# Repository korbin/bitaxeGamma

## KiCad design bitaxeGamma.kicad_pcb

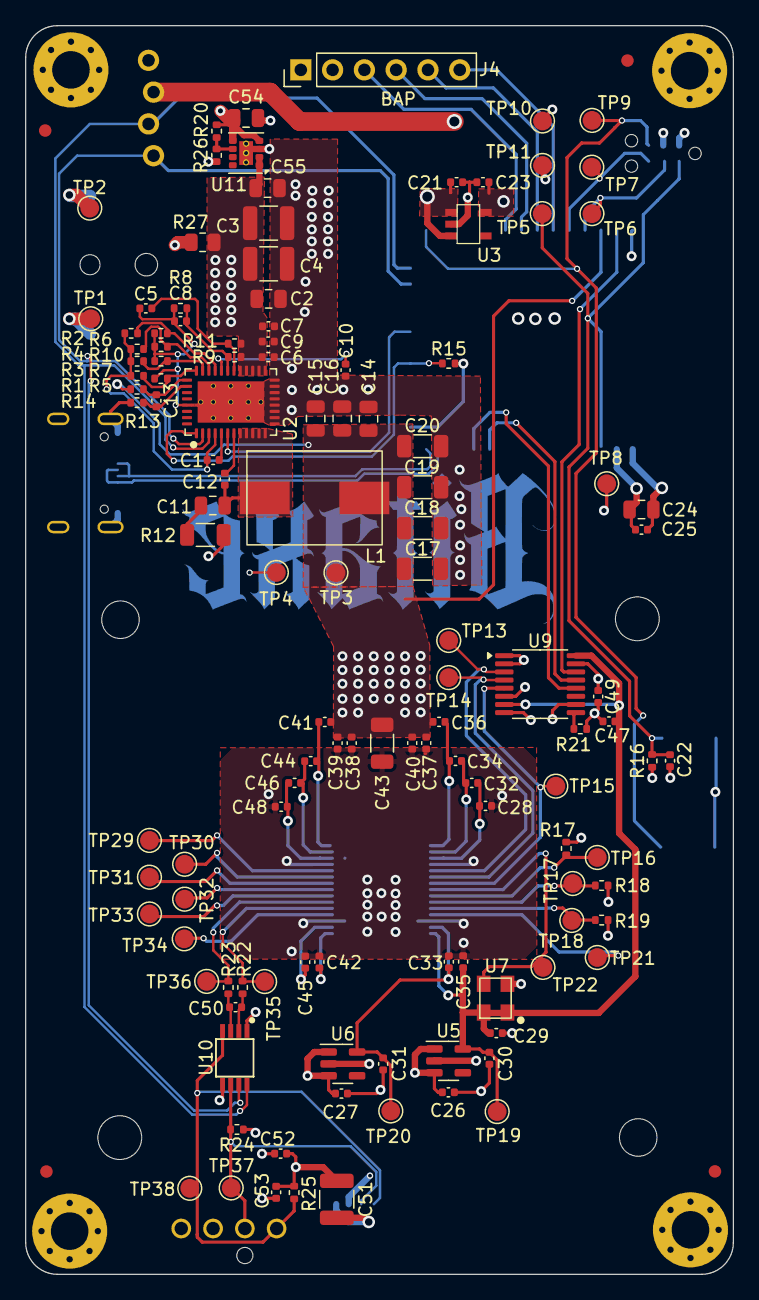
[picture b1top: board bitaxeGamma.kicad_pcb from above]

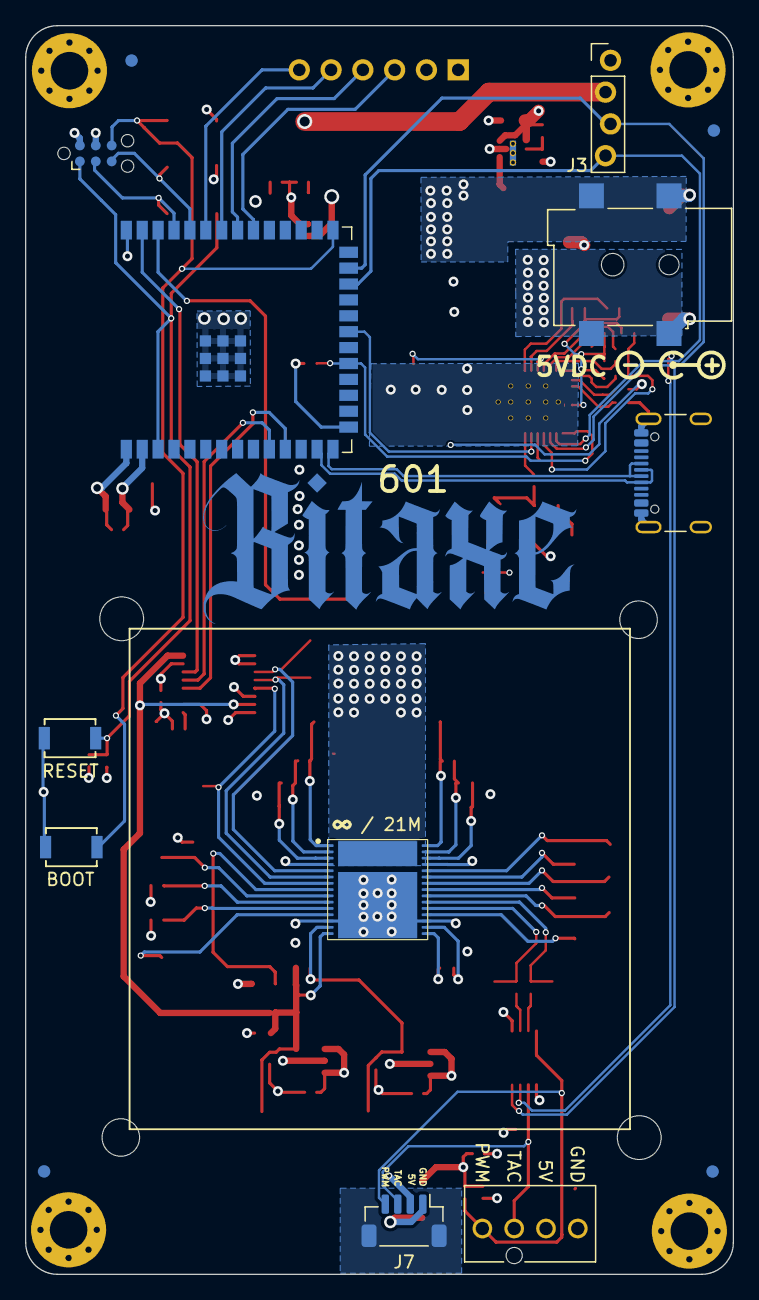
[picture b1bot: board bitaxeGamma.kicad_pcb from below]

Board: 4 copper layers, 56.5 x 99.8 mm, 151 parts (15 on the bottom side), 69 nets.

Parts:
C1, C5, C7, C21, C22, C23, C26, C27, C28, C30, C31, C32, C33, C34, C35, C36, C39, C40, C41, C42, C44, C45, C46, C48: 1uF; C_0402_1005Metric
C2, C24: 10uF; C_0805_2012Metric
C3, C4, C51: 47uF; C_1210_3225Metric
C6: 4700pF; C_0402_1005Metric
C8, C12, C25, C29, C37, C38, C47, C49, C52, C53: 0.1uF; C_0402_1005Metric
C9: 2200pF; C_0402_1005Metric
C10: 4.7uF; C_0402_1005Metric
C11: 1000pF; C_0805_2012Metric
C13: 100pF; C_0402_1005Metric
C14, C15, C16, C54, C55: 22uF; C_0805_2012Metric
C17, C18, C19, C20, C43: 100uF; C_1206_3216Metric
C50: 470pF; C_0402_1005Metric
FID1, FID2, FID3, FID4, FID5, FID6, FID7, FID8: Fiducial; Fiducial_1mm_Mask2mm
H1, H2, H3, H4: MountingHole_Pad; MountingHole_3mm_Pad_Via
H5, H6, H7, H8: MountingHole; MountingHole_3.5mm
J1: 54-00164; TENSILITY_54-00164
J2: TC2030-IDC; Tag-Connect_TC2030-IDC-NL_2x03_P1.27mm_Vertical
J3: Conn_01x04; PinHeader_1x04_P2.54mm_Vertical_shifted
J4: Conn_01x06; PinHeader_1x06_P2.54mm_Vertical
J5: USB_C_Receptacle_USB2.0; USB_C_Receptacle_GCT_USB4105-xx-A
J6: Conn_01x04; 470531000
J7: Conn_01x04; JST_SH_BM04B-SRSS-TB_1x04-1MP_P1.00mm_Vertical
L1: 300nH; SLC1175-271MEC_COC
R1: 8.25k; R_0402_1005Metric
R2, R3, R4, R7: R_0402_1005Metric
R5, R26: 14.7k; R_0402_1005Metric
R6: 0; R_0402_1005Metric
R8: 3.74k; R_0402_1005Metric
R9: 11.8k; R_0402_1005Metric
R10, R20: 68.1k; R_0402_1005Metric
R11: 10; R_0402_1005Metric
R12: 1; R_1206_3216Metric
R13, R14: 49.9; R_0402_1005Metric
R15, R16, R17, R25: 10k; R_0402_1005Metric
R18, R19: 1k; R_0402_1005Metric
R21: 20k; R_0402_1005Metric
R22, R23: 100; R_0402_1005Metric
R24: 5.6k; R_0402_1005Metric
R27: 0; R_0805_2012Metric
SW1, SW2: GT-TC029B-H025-L1N; SW_CS1213AGF260_CRS
T1: net-tie; NetTie-0.25mm
TP1, TP2, TP3, TP4, TP5, TP6, TP7, TP8, TP9, TP10, TP11, TP13, TP14, TP15, TP16, TP17, TP18, TP19, TP20, TP21, TP22, TP29, TP30, TP31, TP32, TP33, TP34, TP35, TP36, TP37, TP38: TestPoint; TestPoint_Pad_D1.5mm
U1: polarity
U2: TPS546D24ARVFR; LQFN40-CLIP
U3: RT9080-33GJ5
U4: ESP32-S3-WROOM-1
U5: MCP1824T-1202E/OT; SOT-23-5
U6: MCP1824T-0802E; SOT-23-5
U7: 25MHz; SMD3225-4P
U8: BM1370_mode1; BM1370
U9: SN74AVC4T774; TSSOP-16_4.4x5mm_P0.65mm
U10: EMC2101; TSSOP-8_3x3mm_P0.65mm
U11: TPS82130; Texas_SIL0008D_MicroSiP-8-1EP_2.8x3mm_P0.65mm_EP1.1x1.9mm_T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

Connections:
/3V3: C23.1, C24.1, C25.1, C49.1, J2.2, J3.2, R15.2, R16.1, R24.2, TP8.1, TP11.1, U3.5 (VOUT), U4.2 (3V3), U4.15 (GPIO3/TOUCH3/ADC1_CH2*), U9.15 (VCCB), U10.1 (VDD)
/5V: C21.1, C26.1, C27.1, C51.1, C52.1, C53.1, C54.1, J4.1, J6.2, J7.2, R20.1, R25.2, R27.2, U3.1 (VIN), U3.3 (EN), U5.1 (VIN), U5.3 (EN), U6.1 (VIN), U6.3 (EN), U11.4 (VOUT), U11.5 (VOUT)
/BM1370/0V8: C31.1, C33.1, TP20.1, U6.5 (VOUT), U8.14 (VDDIO_08_0)
/BM1370/1V2: C29.2, C30.1, C35.1, C47.1, TP19.1, U5.5 (VOUT), U7.1 (EN), U7.4 (VIN), U8.15 (VDDIO_12_0), U9.7 (DIR3), U9.16 (VCCA)
/BM1370/BI: R17.2, TP16.1, U8.9 (BI)
/BM1370/BO: TP33.1, U8.22 (BO)
/BM1370/CI: TP14.1, U8.6 (CI), U9.4 (A2)
/BM1370/CLKI: TP22.1, U7.3 (OUT), U8.8 (CLKI)
/BM1370/CLKO: TP32.1, U8.23 (CLKO)
/BM1370/CO: TP30.1, U8.25 (CO)
/BM1370/NRSTO: TP29.1, U8.26 (NRSTO)
/BM1370/PIN_MODE: TP34.1, U8.19 (PIN_MODE)
/BM1370/RI: TP31.1, U8.24 (RI)
/BM1370/RO: TP15.1, U8.7 (RO), U9.5 (A3)
/BM1370/RST_N: TP13.1, U8.5 (NRSTI), U9.3 (A1)
/BM1370/VDD1_0: C34.2, C36.1, U8.1 (VDD3_0)
/BM1370/VDD1_1: C41.2, C44.1, U8.30 (VDD3_1)
/BM1370/VDD2_0: C32.2, C34.1, U8.2 (VDD2_0)
/BM1370/VDD2_1: C44.2, C46.1, U8.29 (VDD2_1)
/BM1370/VDD3_0: C28.2, C32.1, U8.3 (VDD1_0)
/BM1370/VDD3_1: C46.2, C48.1, U8.28 (VDD1_1)
/ESP32/EN: C22.1, J2.1, R16.2, SW1.2, TP5.1, U4.3 (EN)
/ESP32/IO0: J2.6, SW2.2, TP9.1, U4.27 (GPIO0/BOOT*)
/ESP32/P_RX: J2.5, TP7.1, U4.36 (U0RXD/GPIO44/CLK_OUT2)
/ESP32/P_TX: J2.3, TP6.1, U4.37 (U0TXD/GPIO43/CLK_OUT1)
/ESP32/USB_D+: J5.A6 (D+), J5.B6 (D+), U4.14 (GPIO20/U1CTS/ADC2_CH9/CLK_OUT1/USB_D+)
/ESP32/USB_D-: J5.A7 (D-), J5.B7 (D-), U4.13 (GPIO19/U1RTS/ADC2_CH8/CLK_OUT2/USB_D-)
/Fan/FAN_PWM: J6.4, J7.4, R25.1, TP38.1, U10.4 (FAN)
/Fan/FAN_TACH: J6.3, J7.3, R24.1, TP37.1, U10.6 (ALERT/TACH)
/Fan/TEMP_DN: C50.2, R22.1, U10.3 (DN)
/Fan/TEMP_DP: C50.1, R23.2, U10.2 (DP)
/Fan/TEMP_N: R22.2, TP36.1, U8.21 (TEMP_N)
/Fan/TEMP_P: R23.1, TP35.1, U8.20 (TEMP_P)
/Power/AGND: C5.1, C8.2, R5.1, R6.2, R7.2, R8.2, R10.2, T1.1, U2.37 (AGND)
/Power/PGOOD: R15.1, U2.1 (PGD), U4.19 (GPIO11/TOUCH11/ADC2_CH0/FSPID/FSPIIO5/S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)
/Power/PMB_ALRT: U2.6 (SMB_ALRT), U4.21 (GPIO13/TOUCH13/ADC2_CH2/FSPIQ/FSPIIO7/S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)
/Power/SW: C11.2, C12.2, L1.1, U2.8 (SW), U2.9 (SW), U2.10 (SW), U2.11 (SW), U2.12 (SW)
/Power/VIN: C2.1, C3.1, C4.1, C6.1, C7.1, C9.1, C55.1, J1.1, R9.1, R11.1, R27.1, TP1.1, U2.21 (PVIN), U2.22 (PVIN), U2.23 (PVIN), U2.24 (PVIN), U2.25 (PVIN), U11.1 (EN), U11.2 (VIN)
/RST: U4.39 (GPIO1/TOUCH1/ADC1_CH0), U9.14 (B1)
/RX: U4.11 (GPIO18/U1RXD/ADC2_CH7/CLK_OUT3), U9.12 (B3)
/SCL: J3.3, U2.3 (PMB_CLK), U4.25 (GPIO48/SPICLK_N/SUBSPICLK_N_DIFF), U10.8 (SMCLK)
/SDA: J3.4, U2.2 (PMB_DATA), U4.24 (GPIO47/SPICLK_P/SUBSPICLK_P_DIFF), U10.7 (SMDATA)
/TX: U4.10 (GPIO17/U1TXD/ADC2_CH6), U9.13 (B2)
/VDD: C14.1, C15.1, C16.1, C17.1, C18.1, C19.1, C20.1, C36.2, C37.1, C38.1, C39.1, C40.1, C41.1, C43.1, L1.2, R14.1, TP3.1, U4.38 (GPIO2/TOUCH2/ADC1_CH1), U8.31 (VDD)
GND: C2.2, C3.2, C4.2, C6.2, C7.2, C9.2, C10.2, C14.2, C15.2, C16.2, C17.2, C18.2, C19.2, C20.2, C21.2, C22.2, C23.2, C24.2, C25.2, C26.2, C27.2, C28.1, C29.1, C30.2, C31.2, C33.2, C35.2, C37.2, C38.2, C39.2, C40.2, C42.2, C43.2, C45.2, C47.2, C48.2, C49.2, C51.2, C52.2, C53.2, C54.2, C55.2, H1.1, H2.1, H3.1, H4.1, J1.2, J1.3, J2.4, J3.1, J4.2, J5.A1 (GND), J5.B1 (GND), J5.S1 (SHIELD), J6.1, J7.1, R12.1, R13.2, R17.1, R18.1, R19.1, R21.1, R26.1, SW1.1, SW2.1, T1.2, TP2.1, TP4.1, TP10.1, U2.13 (PGND), U2.14 (PGND), U2.15 (PGND), U2.16 (PGND), U2.17 (PGND), U2.18 (PGND), U2.19 (PGND), U2.20 (PGND), U2.41 (PAD), U3.2 (GND), U4.1 (GND), U4.40 (GND), U4.41 (GND), U5.2 (GND), U6.2 (GND), U7.2 (GND), U8.4 (VSS), U8.13 (PLL_VSS), U8.18 (VSS), U8.27 (VSS), U8.32 (VSS), U9.1 (DIR1), U9.2 (DIR2), U9.6 (A4), U9.8 (DIR4), U9.10 (GND), U10.5 (GND), U11.3 (GND), U11.9 (GND)
unnamed: C11.1, R12.2
unnamed: J4.3, U4.32 (MTCK/GPIO39/CLK_OUT3/SUBSPICS1)
unnamed: J4.4, U4.33 (MTDO/GPIO40/CLK_OUT2)
unnamed: J4.5, U4.34 (MTDI/GPIO41/CLK_OUT1)
unnamed: J4.6, U4.35 (MTMS/GPIO42)
unnamed: R3.2, R7.1, U2.31 (ADRSEL)
unnamed: C5.2, R11.2, U2.26 (AVIN)
unnamed: C12.1, U2.7 (BOOT)
unnamed: C1.2, R1.1, R2.1, R3.1, R4.1, U2.4 (BP1V5)
unnamed: C1.1, U2.5 (DRTN)
unnamed: C8.1, R8.1, R9.2, U2.27 (EN/UVLO)
unnamed: C13.2, R13.1, U2.34 (GOSNS)
unnamed: R1.2, R5.2, U2.32 (MSEL1)
unnamed: R2.2, R6.1, U2.29 (MSEL2)
unnamed: C10.1, U2.28 (VDD5)
unnamed: C13.1, R14.2, U2.33 (VOSNS)
unnamed: R4.2, R10.1, U2.30 (VSEL)
unnamed: TP21.1, U8.12 (INV_CLKO)
unnamed: R19.2, TP18.1, U8.11 (LITE_PAD)
unnamed: R18.2, TP17.1, U8.10 (ROSC_SEL)
unnamed: C45.1, U8.17 (VDDIO_08_1)
unnamed: C42.1, U8.16 (VDDIO_12_1)
unnamed: R21.2, U9.9 (OE)
unnamed: R20.2, R26.2, U11.6 (FB)

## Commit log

2026-02-22 add tps82130 for wide-VIN support
2026-02-22 add 0805 0R fallback jumper from VIN->5V
2026-02-22 fork sil0008d footprint to fix pad sizes
